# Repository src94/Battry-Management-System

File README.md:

# Battry-Management-System
BMS for a 12S Li-ion battery pack.
This BMS uses LTC6803 balancing IC to be used for a 12S battery pack.
The MCU used is an AtMega328P-PU, which is responsible for protecting the battery pack from overcurrent condition during cgarging and discharging. It will also calculate the SOC and SOH of the pack.
A hall effect current sensor is used to read the current while charging and discharging.
Columb counting is done to keep track of the SOC and DOD.
The SOC and DOD values can be stored in a flash memory to keep track of battery health.

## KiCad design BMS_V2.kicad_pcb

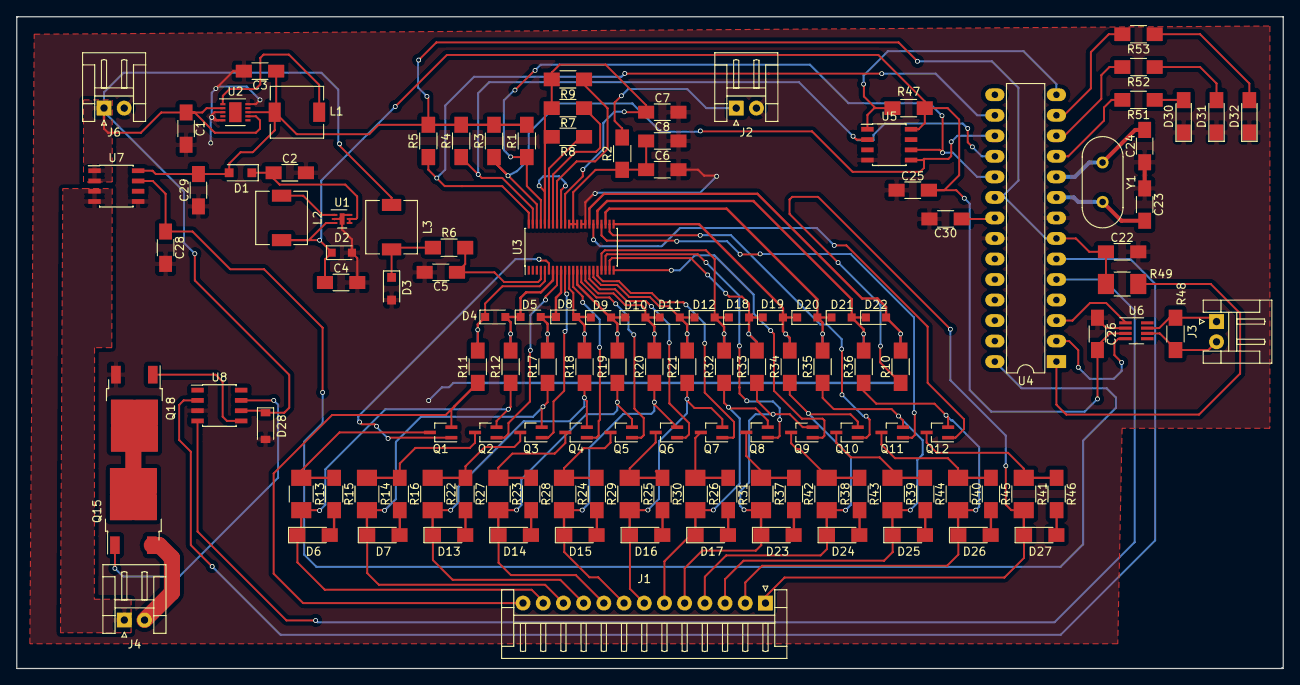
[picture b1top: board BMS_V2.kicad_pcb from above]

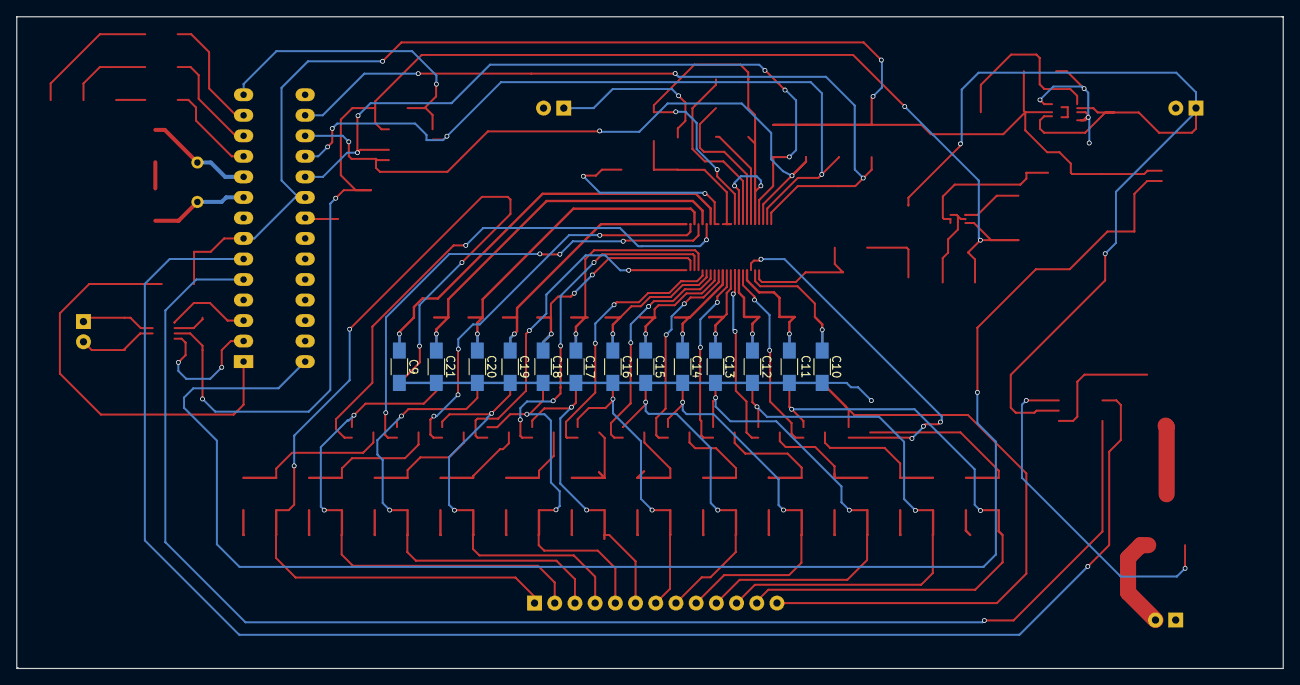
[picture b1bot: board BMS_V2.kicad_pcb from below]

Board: 2 copper layers, 156.7 x 80.6 mm, 143 parts (13 on the bottom side), 104 nets.

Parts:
C1, C6, C7, C8, C29: 1U; C_1206_HandSoldering
C2, C4: 10U; C_1206_HandSoldering
C3: 22U; C_1206_HandSoldering
C5, C9, C10, C11, C12, C13, C14, C15, C16, C17, C18, C19, C20, C21, C25, C26, C28: 0.1U; C_1206_HandSoldering
C22, C23, C24, C30: 100nF; C_1206_HandSoldering
D1: PMEG6020ER; D_SOD-123F
D2: SP4020-01FTG; D_SOD-323_HandSoldering
D3: CMHZ5265B TR; D_SOD-123F
D4, D5, D8, D9, D10, D11, D12, D18, D19, D20, D21, D22: MM3Z12VT1G; D_SOD-323_HandSoldering
D6, D7, D13, D14, D15, D16, D17, D23, D24, D25, D26, D27: LED; LED_1206_HandSoldering
D28: 20V Zener; D_SOD-123
D30: CHARGING; LED_1206_HandSoldering
D31: DISCHARGE; LED_1206_HandSoldering
D32: SHORT_CIRCUIT; LED_1206_HandSoldering
J1: BALANCING; JST_EH_S13B-EH_13x2.50mm_Angled
J2: TEMP; JST_EH_S02B-EH_02x2.50mm_Angled
J3: CAN OUT; JST_EH_S02B-EH_02x2.50mm_Angled
J4: BATT_DCH; JST_EH_S02B-EH_02x2.50mm_Angled
J6: BATT_IN; JST_EH_S02B-EH_02x2.50mm_Angled
L1: 68U; L_6.3x6.3_H3
L2: 22U; L_6.3x6.3_H3
L3: 33U; L_6.3x6.3_H3
Q1, Q2, Q3, Q4, Q5, Q6, Q7, Q8, Q9, Q10, Q11, Q12: BSS84PWH6327XTSA1; SOT-323_SC-70_Handsoldering
Q15, Q18: 240N75F3; TO-252-2
R1, R3, R4, R7, R8, R9: 1M; R_1206_HandSoldering
R2: 100K; R_1206_HandSoldering
R5, R51, R52, R53: 1K; R_1206_HandSoldering
R6, R10, R11, R12, R15, R16, R17, R18, R19, R20, R21, R27, R28, R29, R30, R31, R32, R33, R34, R35, R36, R42, R43, R44, R45, R46: 100; R_1206_HandSoldering
R13, R14, R22, R23, R24, R25, R26, R37, R38, R39, R40, R41: 47; R_1210_HandSoldering
R47: 10K; R_1206_HandSoldering
R48: 120; R_1206_HandSoldering
R49: 10K; R_1210_HandSoldering
U1: TPS62291DRVR; DFN-6-1EP_2x2mm_Pitch0.5mm
U2: LM5165; DFN-10-1EP_3x3mm_Pitch0.5mm
U3: LTC6803IG-3; TSSOP-44_4.4x11.2mm_Pitch0.5mm
U4: ATMEGA328P-PU; DIP-28_W7.62mm_LongPads
U5: AT25SF081; SOIC-8_3.9x4.9mm_Pitch1.27mm
U6: TCAN332DCNR; SOT-23-8_Handsoldering
U7: ACS711xLCTR-25AB; SOIC-8_3.9x4.9mm_Pitch1.27mm
U8: MIC4427; SOIC-8_3.9x4.9mm_Pitch1.27mm
Y1: Crystal; Crystal_HC49-U_Vertical

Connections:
+3V3: C4.1, C25.2, C26.2, D2.1, L2.2, R47.1, U1.3, U5.8, U6.3
+5V: C3.1, C22.1, C29.2, D1.2, L1.2, R1.2, R3.2, R4.2, R5.2, R49.1, U2.8, U4.7, U4.20, U7.8
/BATTERY PROTECTION/CHG_SIG: U4.6, U8.2
/BATTERY PROTECTION/CURRENT: C28.1, U4.28, U7.7
/BATTERY PROTECTION/DCH_SIG: U4.5, U8.4
/CAN/CANH: J3.1, R48.1, U6.7
/CAN/CANL: J3.2, R48.2, U6.6
/CAN/RX: U4.2, U6.4
/CAN/TX: U4.3, U6.1
/FLASH MEMORY/CS2: R47.2, U4.14, U5.1
/FLASH MEMORY/MISO: R4.1, U3.43, U4.18, U5.2
/FLASH MEMORY/MOSI: R3.1, U3.42, U4.17, U5.5
/FLASH MEMORY/SCK: R1.1, U3.41, U4.19, U5.6
/LTC6803/CELL BALANCING/C0: C9.1, D22.2, R10.2, U3.29
/LTC6803/CELL BALANCING/C1: C21.1, D21.2, D22.1, R36.2, U3.27
/LTC6803/CELL BALANCING/C2: C20.1, D20.2, D21.1, R35.2, U3.25
/LTC6803/CELL BALANCING/C3: C19.1, D19.2, D20.1, R34.2, U3.23
/LTC6803/CELL BALANCING/C4: C18.1, D18.2, D19.1, R33.2, U3.21
/LTC6803/CELL BALANCING/C5: C17.1, D12.2, D18.1, R32.2, U3.19
/LTC6803/CELL BALANCING/C6: C16.1, D11.2, D12.1, R21.2, U3.17
/LTC6803/CELL BALANCING/C7: C15.1, D10.2, D11.1, R20.2, U3.15
/LTC6803/CELL BALANCING/C8: C14.1, D9.2, D10.1, R19.2, U3.13
/LTC6803/CELL BALANCING/C9: C13.1, D8.2, D9.1, R18.2, U3.11
/LTC6803/CELL BALANCING/C10: C12.1, D5.2, D8.1, R17.2, U3.9
/LTC6803/CELL BALANCING/C11: C11.1, D4.2, D5.1, R12.2, U3.7
/LTC6803/CELL BALANCING/C12: C10.1, D4.1, R11.2, U3.5
/LTC6803/CELL BALANCING/CTRL1: Q12.1, U3.28
/LTC6803/CELL BALANCING/CTRL2: Q11.1, U3.26
/LTC6803/CELL BALANCING/CTRL3: Q10.1, U3.24
/LTC6803/CELL BALANCING/CTRL4: Q9.1, U3.22
/LTC6803/CELL BALANCING/CTRL5: Q8.1, U3.20
/LTC6803/CELL BALANCING/CTRL6: Q7.1, U3.18
/LTC6803/CELL BALANCING/CTRL7: Q6.1, U3.16
/LTC6803/CELL BALANCING/CTRL8: Q5.1, U3.14
/LTC6803/CELL BALANCING/CTRL9: Q4.1, U3.12
/LTC6803/CELL BALANCING/CTRL10: Q3.1, U3.10
/LTC6803/CELL BALANCING/CTRL11: Q2.1, U3.8
/LTC6803/CELL BALANCING/CTRL12: Q1.1, U3.6
/LTC6803/CS1: R5.1, U3.44, U4.16
CELL0: D27.1, J1.1, R10.1, R41.2
CELL1: D26.1, J1.2, Q12.2, R36.1, R40.2
CELL2: D25.1, J1.3, Q11.2, R35.1, R39.2
CELL3: D24.1, J1.4, Q10.2, R34.1, R38.2
CELL4: D23.1, J1.5, Q9.2, R33.1, R37.2
CELL5: D17.1, J1.6, Q8.2, R26.2, R32.1
CELL6: D16.1, J1.7, Q7.2, R21.1, R25.2
CELL7: D15.1, J1.8, Q6.2, R20.1, R24.2
CELL8: D14.1, J1.9, Q5.2, R19.1, R23.2
CELL9: D13.1, J1.10, Q4.2, R18.1, R22.2
CELL10: D7.1, J1.11, Q3.2, R14.2, R17.1
CELL11: D6.1, J1.12, Q2.2, R12.1, R13.2
CELL12: J1.13, Q1.2, R11.1
NTC: J2.1, R2.2
unnamed: C2.1, D1.1, U1.4, U1.5
unnamed: C5.1, R6.2, U3.4
unnamed: C6.1, C8.1, R2.1, U3.32, U3.33, U3.34
unnamed: C7.1, R7.2, R8.2, R9.2, U3.35, U3.36, U3.40
unnamed: C23.2, U4.9, Y1.2
unnamed: C24.2, U4.10, Y1.1
unnamed: C30.1, U4.21
unnamed: D3.1, L3.2, R6.1
unnamed: D6.2, R15.2
unnamed: D7.2, R16.2
unnamed: D13.2, R27.2
unnamed: D14.2, R28.2
unnamed: D15.2, R29.2
unnamed: D16.2, R30.2
unnamed: D17.2, R31.2
unnamed: D23.2, R42.2
unnamed: D24.2, R43.2
unnamed: D25.2, R44.2
unnamed: D26.2, R45.2
unnamed: D27.2, R46.2
unnamed: D30.2, R51.1
unnamed: D31.2, R52.1
unnamed: D32.2, R53.1
unnamed: L1.1, U2.1
unnamed: L2.1, U1.1
unnamed: Q1.3, R13.1, R15.1
unnamed: Q2.3, R14.1, R16.1
unnamed: Q3.3, R22.1, R27.1
unnamed: Q4.3, R23.1, R28.1
unnamed: Q5.3, R24.1, R29.1
unnamed: Q6.3, R25.1, R30.1
unnamed: Q7.3, R26.1, R31.1
unnamed: Q8.3, R37.1, R42.1
unnamed: Q9.3, R38.1, R43.1
unnamed: Q10.3, R39.1, R44.1
unnamed: Q11.3, R40.1, R45.1
unnamed: Q12.3, R41.1, R46.1
unnamed: Q15.1, U8.7
unnamed: Q15.2, Q18.2
unnamed: Q18.1, U8.5
unnamed: R7.1, U3.38
unnamed: R8.1, U3.39
unnamed: R9.1, U3.37
unnamed: R49.2, U4.1
unnamed: R51.2, U4.11
unnamed: R52.2, U4.12
unnamed: R53.2, U4.13
V+: C1.1, D28.1, J6.1, L3.1, U2.2, U2.7, U7.1, U7.2, U8.6
V+_OUT: J4.1, U7.3, U7.4
V-: C1.2, C2.2, C3.2, C4.2, C5.2, C6.2, C7.2, C8.2, C9.2, C10.2, C11.2, C12.2, C13.2, C14.2, C15.2, C16.2, C17.2, C18.2, C19.2, C20.2, C21.2, C22.2, C23.1, C24.1, C25.1, C26.1, C28.2, C29.1, C30.2, D2.2, D3.2, D28.2, D30.1, D31.1, D32.1, J2.2, J6.2, Q18.3, U1.2, U1.6, U1.7, U2.3, U2.5, U2.10, U3.30, U3.31, U4.8, U4.22, U5.4, U6.2, U7.5, U8.3
V-_OUT: J4.2, Q15.3

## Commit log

2018-04-28 Create LICENSE
